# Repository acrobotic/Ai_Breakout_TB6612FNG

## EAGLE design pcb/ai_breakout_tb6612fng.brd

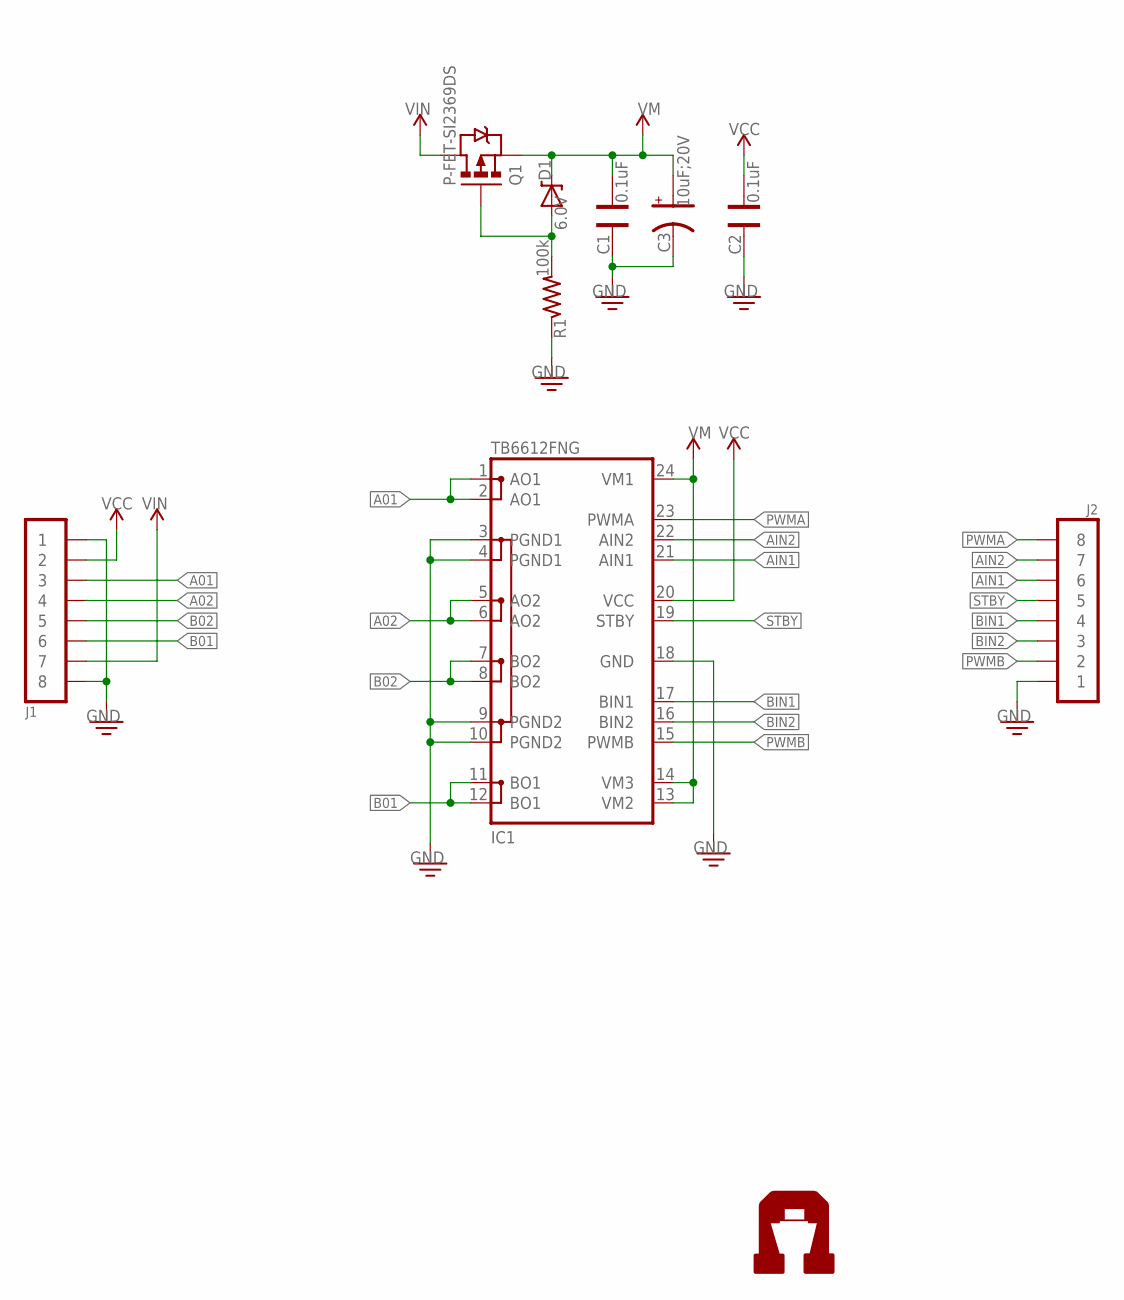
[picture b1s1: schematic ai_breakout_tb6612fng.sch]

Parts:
C1, C2: 0.1uF; CAP-0603
C3: 10uF;20V; CAP-POL-EIA3216
D1: 6.0V; SOD-323
IC1: TB6612FNG; SSOP24
J1: 1X08
J2: 1X08NOFIRST; 1X08-NOFIRST
Q1: P-FET-SI2369DS; SOT-23
R1: 100k; RES-0603
U$5: AI-LOGOXS; AI-LOGO-XS

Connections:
A01: IC1.1 (AO1), IC1.2 (AO1), J1.3
A02: IC1.5 (AO2), IC1.6 (AO2), J1.4
AIN1: IC1.21 (AIN1), J2.6
AIN2: IC1.22 (AIN2), J2.7
B01: IC1.11 (BO1), IC1.12 (BO1), J1.6
B02: IC1.7 (BO2), IC1.8 (BO2), J1.5
BIN1: IC1.17 (BIN1), J2.4
BIN2: IC1.16 (BIN2), J2.3
GND: C1.2, C2.2, C3.C, IC1.3 (PGND1), IC1.4 (PGND1), IC1.9 (PGND2), IC1.10 (PGND2), IC1.18 (GND), J1.1, J1.8, J2.1, R1.1
unnamed: D1.A, Q1.1 (G), R1.2
PWMA: IC1.23 (PWMA), J2.8
PWMB: IC1.15 (PWMB), J2.2
STBY: IC1.19 (STBY), J2.5
VCC: C2.1, IC1.20 (VCC), J1.2
VIN: J1.7, Q1.3 (D)
VM: C1.1, C3.A, D1.C, IC1.13 (VM2), IC1.14 (VM3), IC1.24 (VM1), Q1.2 (S)

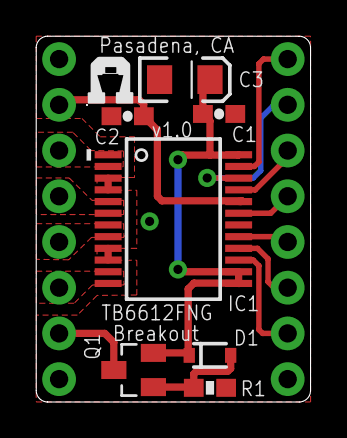
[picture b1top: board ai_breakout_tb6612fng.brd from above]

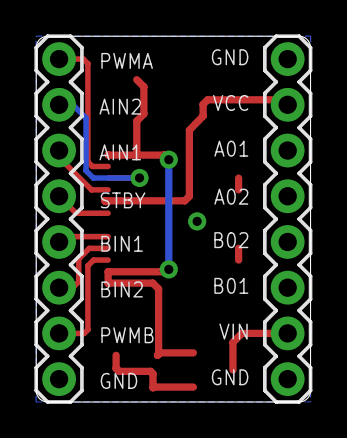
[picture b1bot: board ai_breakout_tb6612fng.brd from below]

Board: 2 copper layers, 15.2 x 20.3 mm, 10 parts (2 on the bottom side), 16 nets.
